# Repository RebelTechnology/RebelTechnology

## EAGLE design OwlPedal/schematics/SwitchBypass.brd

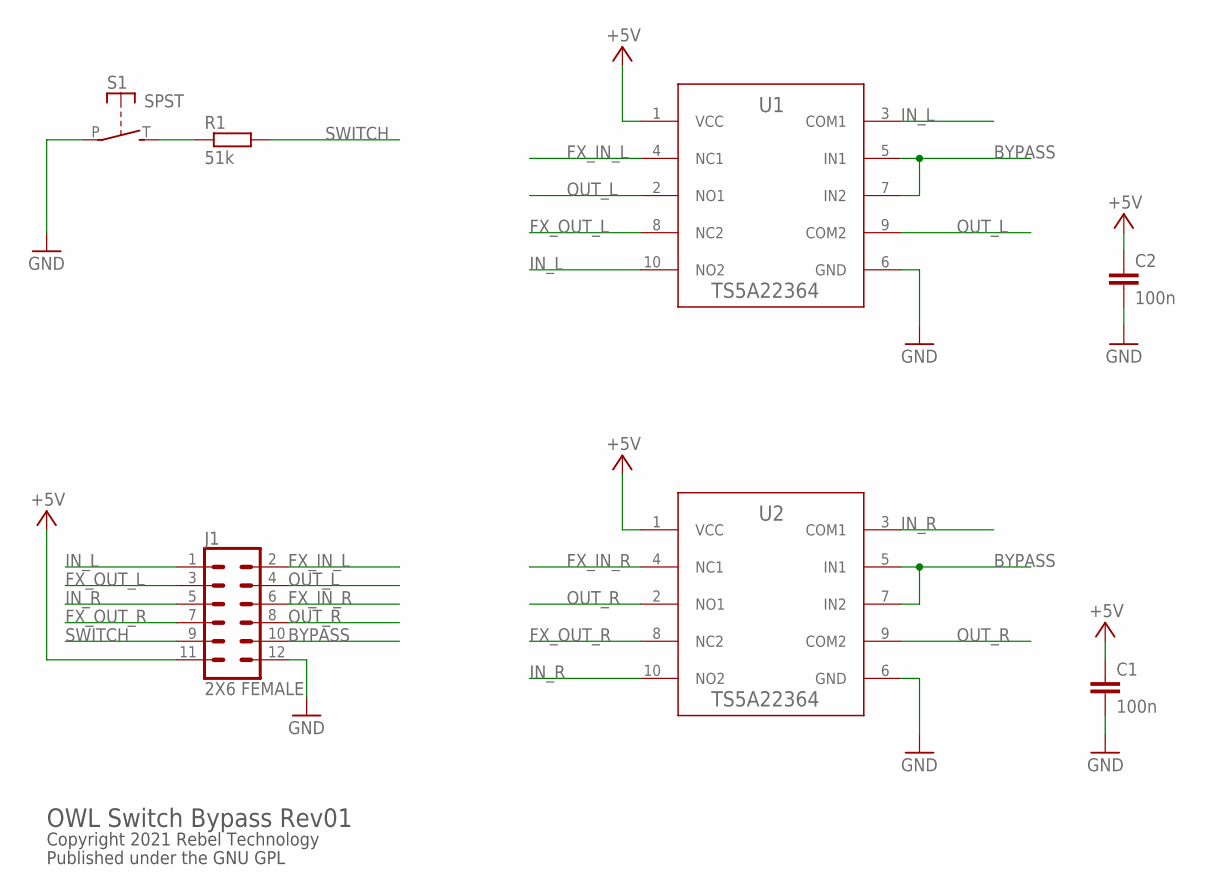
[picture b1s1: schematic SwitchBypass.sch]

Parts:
C1, C2: 100n; C0603
J1: 2X6 FEMALE; 2X6
R1: 51k; 0603
S1: SPST; JUDCOSPST
U1, U2: TS5A22364; DGS0010A_L

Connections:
+5V: C1.1, C2.1, J1.11, U1.1 (VCC), U2.1 (VCC)
BYPASS: J1.10, U1.5 (IN1), U1.7 (IN2), U2.5 (IN1), U2.7 (IN2)
FX_IN_L: J1.2, U1.4 (NC1)
FX_IN_R: J1.6, U2.4 (NC1)
FX_OUT_L: J1.3, U1.8 (NC2)
FX_OUT_R: J1.7, U2.8 (NC2)
GND: C1.2, C2.2, J1.12, S1.P, U1.6 (GND), U2.6 (GND)
IN_L: J1.1, U1.3 (COM1), U1.10 (NO2)
IN_R: J1.5, U2.3 (COM1), U2.10 (NO2)
unnamed: R1.1, S1.T (S)
OUT_L: J1.4, U1.2 (NO1), U1.9 (COM2)
OUT_R: J1.8, U2.2 (NO1), U2.9 (COM2)
SWITCH: J1.9, R1.2

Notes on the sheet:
Copyright 2021 Rebel Technology
Published under the GNU GPL
OWL Switch Bypass Rev01

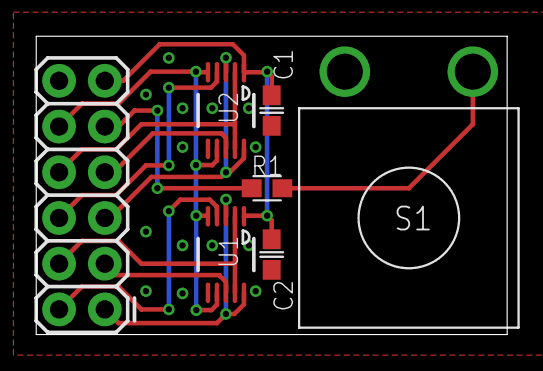
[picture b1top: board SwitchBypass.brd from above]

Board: 2 copper layers, 26.2 x 16.6 mm, 7 parts (0 on the bottom side), 13 nets.

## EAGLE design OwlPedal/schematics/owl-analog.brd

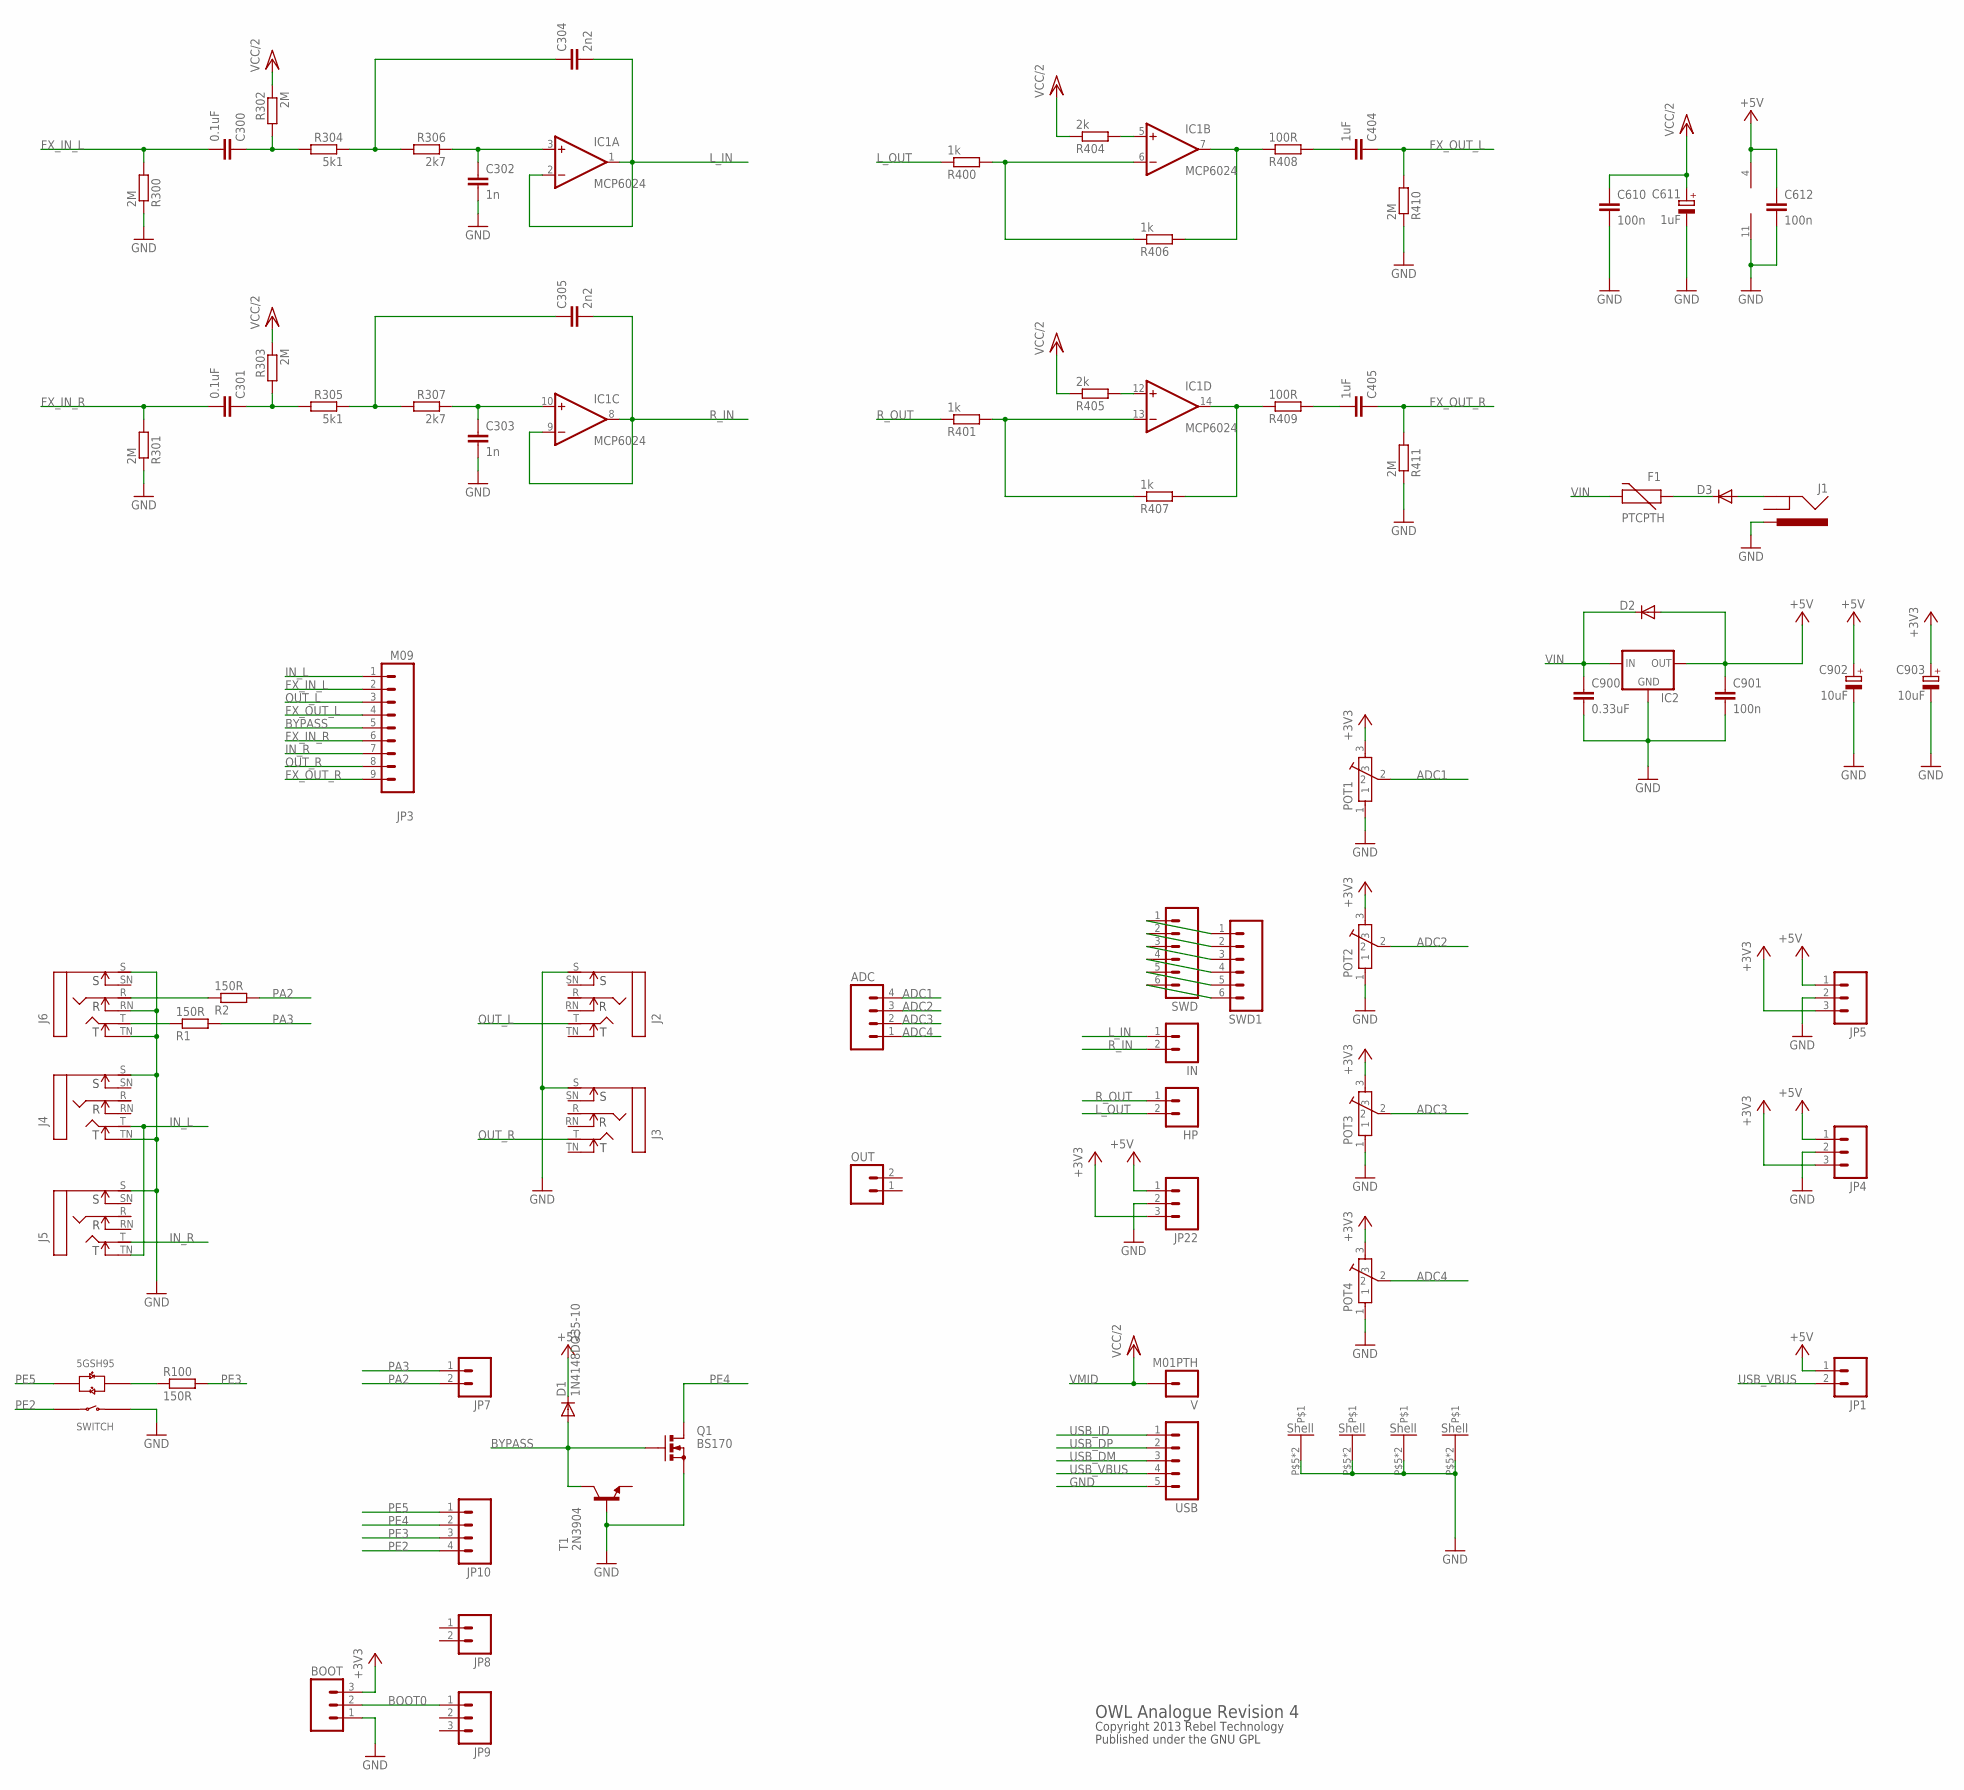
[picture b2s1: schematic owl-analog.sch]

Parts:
ADC: M04PTH; 1X04
BOOT: M03PTH; 1X03
C300, C301: 0.1uF; C5B3.5
C302, C303: 1n; C5B2.5
C304: 2n2; C5B2.5
C305: 2n2; C050-025X075
C404, C405: 1uF; C5B5
C610, C612, C901: 100n; C050-025X075
C611: 1uF; E2,5-7
C900: 0.33uF; C050-025X075
C902, C903: 10uF; E2,5-7
D1: 1N4148DO35-10; DO35-10
D2, D3: DIODE1N4001; DIODE-1N4001
F1: PTCPTH; PTC
HP: M02PTH; 1X02
IC1: MCP6024; DIL14
IC2: V_REG_78XX-TO-220; TO-220-ALT
IN: M02PTH; 1X02
J1: POWER_JACKPTH; POWER_JACK_PTH
J2, J3, J4, J5, J6: NEUTRIK_NMJ6HCD2; NMJ6HCD2
JP1, JP7, JP8: M02PTH; 1X02
JP3: M09; 1X09
JP4, JP5, JP9, JP22: M03PTH; 1X03
JP10: M04PTH; 1X04
OUT: M02PTH; 1X02
POT1, POT2, POT3, POT4: POT-ALPS-RK09L1140
Q1: BS170; SOT54E
R1, R2, R100: 150R; 0204/7
R300, R301, R302, R303, R410, R411: 2M; 0204/7
R304, R305: 5k1; 0204/7
R306, R307: 2k7; 0204/7
R400, R401, R406, R407: 1k; 0204/7
R404, R405: 2k; 0204/7
R408, R409: 100R; 0204/7
SWD, SWD1: M06SIP; 1X06
T1: 2N3904; TO92
U$1: 5GTH9
USB: M05PTH; 1X05
V: M01PTH; 1X01

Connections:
+3V3: BOOT.3, C903.+, JP4.3, JP5.3, JP22.3, POT1.3, POT2.3, POT3.3, POT4.3
+5V: C612.1, C901.1, C902.+, D1.C, D2.A, IC1.4 (V+), IC2.OUT, JP1.1, JP4.1, JP5.1, JP22.1
+5V/1: IC1.5 (+IN), R404.2
ADC1: ADC.4, POT1.2
ADC2: ADC.3, POT2.2
ADC3: ADC.2, POT3.2
ADC4: ADC.1, POT4.2
BOOT0: BOOT.2, JP9.1
BYPASS: D1.A, JP3.5, Q1.G, T1.1 (C)
FX_IN_L: C300.2, JP3.2, R300.2
FX_IN_R: C301.2, JP3.6, R301.2
FX_OUT_L: C404.1, JP3.4, R410.2
FX_OUT_R: C405.1, JP3.9, R411.2
GND: BOOT.1, C302.2, C303.2, C610.2, C611.-, C612.2, C900.2, C901.2, C902.-, C903.-, IC1.11 (V-), IC2.GND, J1.PWR, J2.S, J3.S, J4.S, J4.TN, J5.S, J6.RN, J6.S, J6.TN, JP4.2, JP5.2, JP22.2, POT1.1, POT1.P$5, POT1.P$6, POT2.1, POT2.P$5, POT2.P$6, POT3.1, POT3.P$5, POT3.P$6, POT4.1, POT4.P$5, POT4.P$6, Q1.S, R300.1, R301.1, R410.1, R411.1, T1.2 (B), U$1.1 (SWITCH_B), USB.5
IN_L: J4.T, J5.TN, JP3.1
IN_R: J5.T, JP3.7
L_IN: C304.2, IC1.1 (OUT), IC1.2 (-IN), IN.1
L_OUT: HP.2, R400.1
unnamed: D3.A, J1.GND
unnamed: IC1.12 (+IN), R405.2
unnamed: SWD.1, SWD1.1
unnamed: D3.C, F1.P$1 (1)
unnamed: SWD.2, SWD1.2
unnamed: SWD.3, SWD1.3
unnamed: SWD.4, SWD1.4
unnamed: SWD.5, SWD1.5
unnamed: SWD.6, SWD1.6
unnamed: R100.1, U$1.+3 (LED_R+)
unnamed: J6.R, R2.1
unnamed: J6.T, R1.1
unnamed: C300.1, R302.2, R304.2
unnamed: C405.2, R409.2
unnamed: C301.1, R303.2, R305.2
unnamed: C303.1, IC1.10 (+IN), R307.1
unnamed: C304.1, R304.1, R306.2
unnamed: C305.1, R305.1, R307.2
unnamed: C404.2, R408.2
unnamed: C302.1, IC1.3 (+IN), R306.1
unnamed: IC1.7 (OUT), R406.2, R408.1
unnamed: IC1.14 (OUT), R407.2, R409.1
unnamed: IC1.6 (-IN), R400.2, R406.1
unnamed: IC1.13 (-IN), R401.2, R407.1
OUT_L: J2.T, JP3.3
OUT_R: J3.T, JP3.8
PA2: JP7.2, R2.2
PA3: JP7.1, R1.2
PE2: JP10.4, U$1.4 (SWITCH_A)
PE3: JP10.3, R100.2
PE4: JP10.2, Q1.D
PE5: JP10.1, U$1.-2 (LED_G+)
R_IN: C305.2, IC1.8 (OUT), IC1.9 (-IN), IN.2
R_OUT: HP.1, R401.1
USB_DM: USB.3
USB_DP: USB.2
USB_ID: USB.1
USB_VBUS: JP1.2, USB.4
VIN: C900.1, D2.C, F1.P$2 (2), IC2.IN
VMID: C610.1, C611.+, R302.1, R303.1, R404.1, R405.1, V.1

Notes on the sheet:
Copyright 2013 Rebel Technology
Published under the GNU GPL
OWL Analogue Revision 4

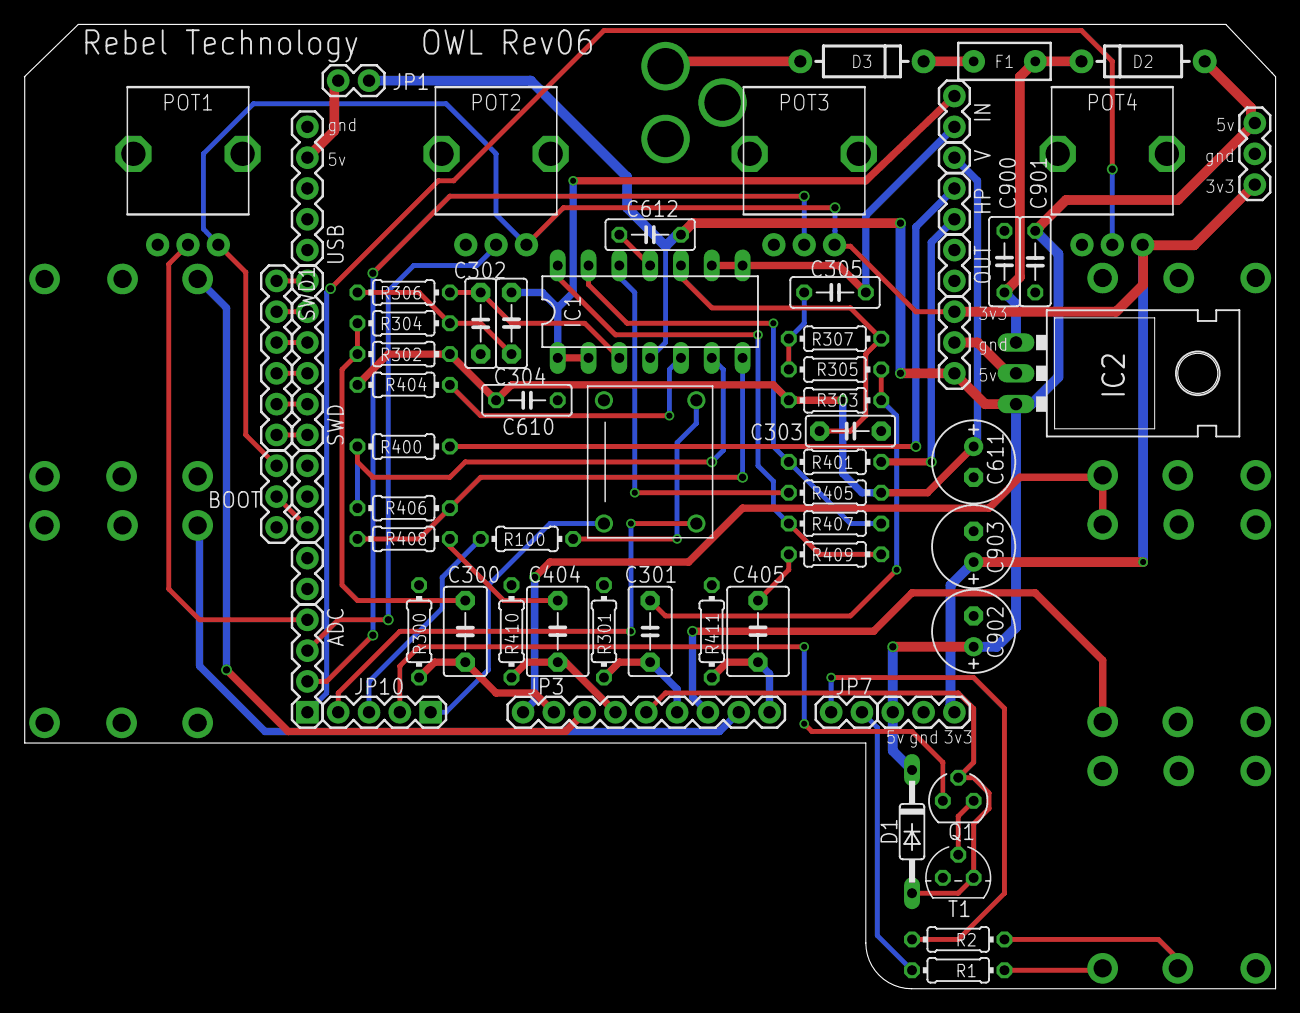
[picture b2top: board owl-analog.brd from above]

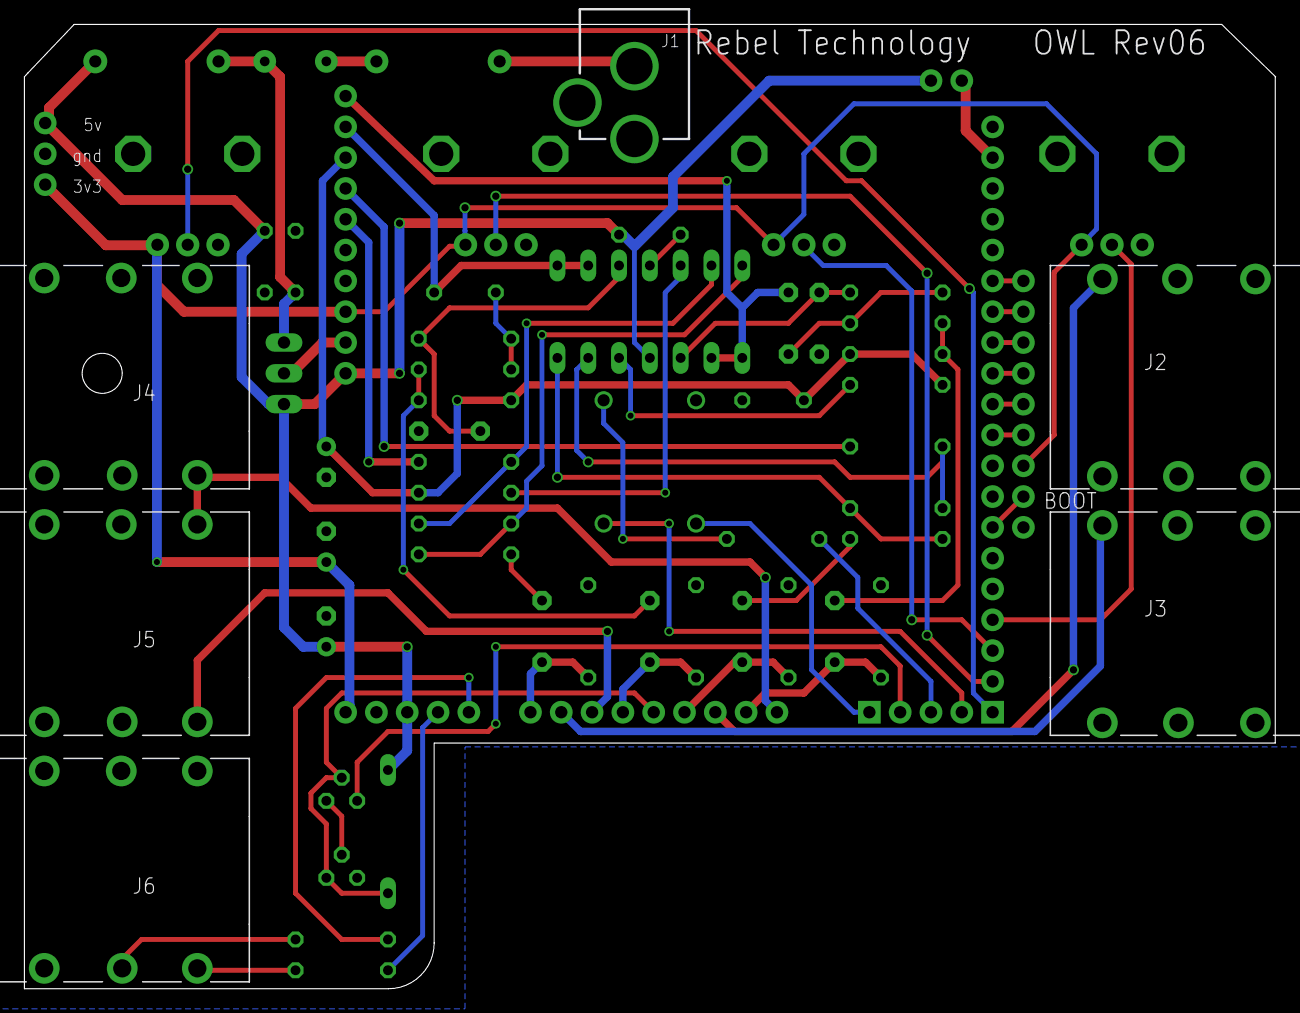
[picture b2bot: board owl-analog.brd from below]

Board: 2 copper layers, 103.1 x 79.5 mm, 73 parts (6 on the bottom side), 55 nets.

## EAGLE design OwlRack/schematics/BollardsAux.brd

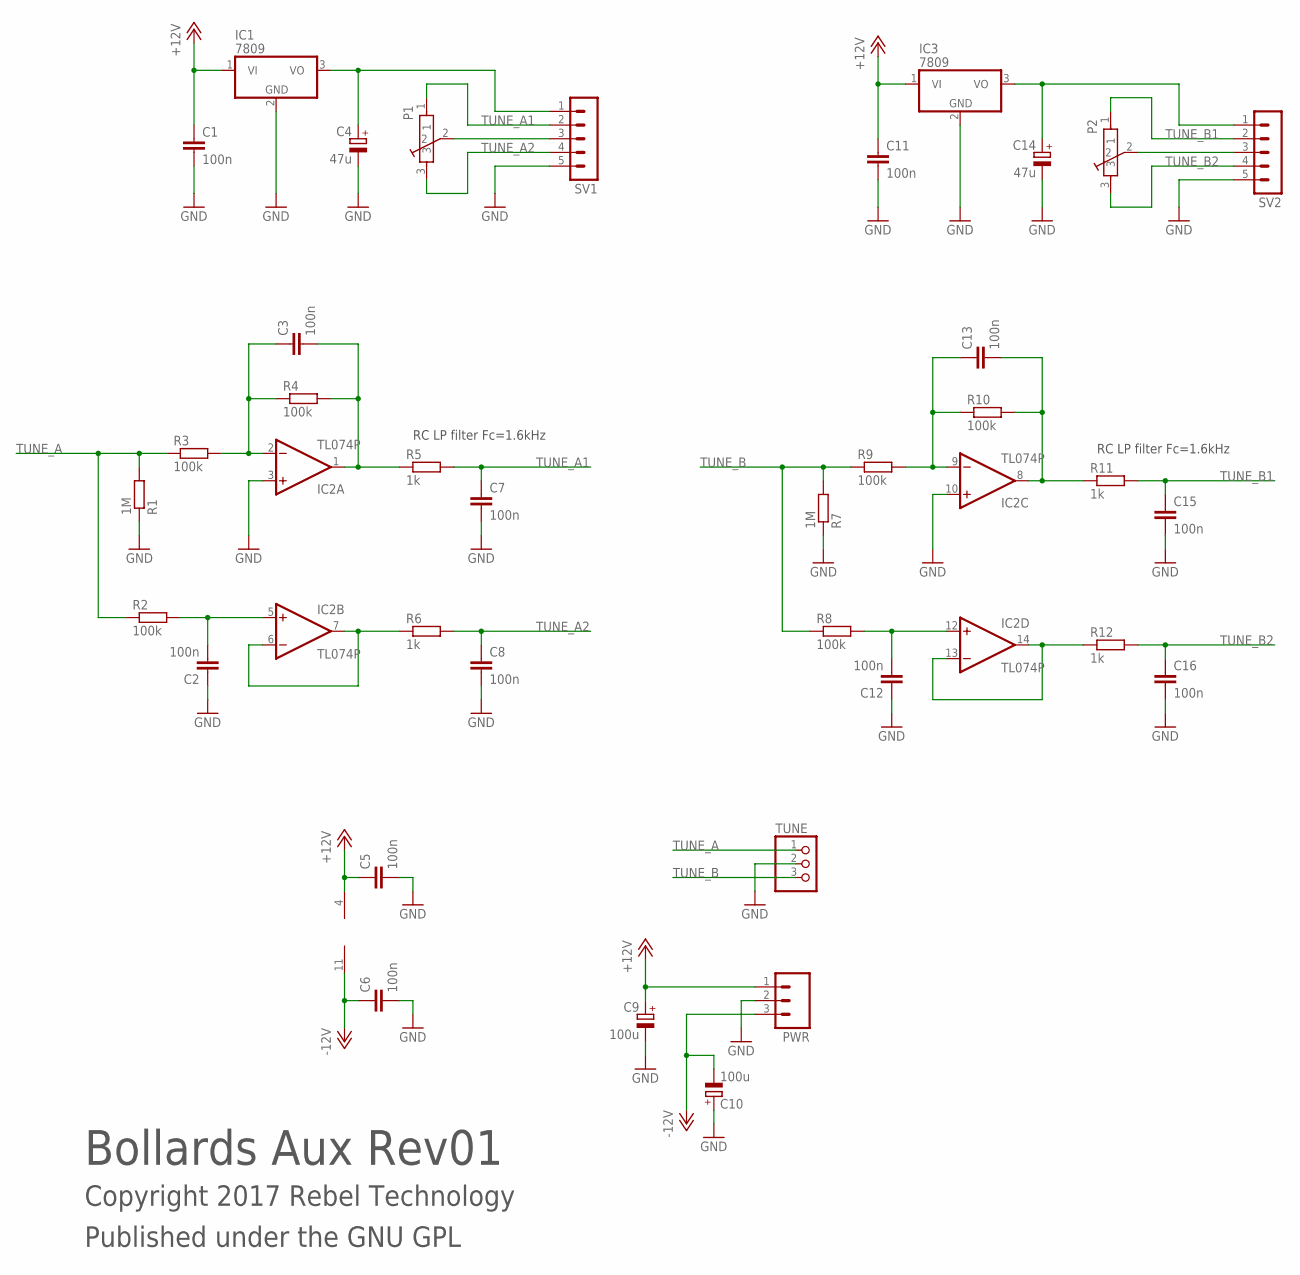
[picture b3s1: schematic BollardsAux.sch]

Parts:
C1, C2, C3, C5, C6, C7, C8, C11, C12, C13, C15, C16: 100n; C050-025X075
C4, C14: 47u; E2,5-7
C9, C10: 100u; E2,5-7
IC1, IC3: 7809; TO220H
IC2: TL074P; DIL14
P1, P2: 100k; POT-BOURNS-PTD901
PWR: M03PTH; 1X03
R1, R7: 1M; 0204/7
R2, R3, R4, R8, R9, R10: 100k; 0204/7
R5, R6, R11, R12: 1k; 0204/7
SV1, SV2: MA05-1
TUNE: CON-JST-1X03PH-TH; JST-B3B-PH-KL

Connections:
+12V: C1.1, C5.1, C9.+, C11.1, IC1.1 (VI), IC2.4 (V+), IC3.1 (VI), PWR.1
-12V: C6.1, C10.-, IC2.11 (V-), PWR.3
GND: C1.2, C2.1, C4.-, C5.2, C6.2, C7.2, C8.2, C9.-, C10.+, C11.2, C12.1, C14.-, C15.2, C16.2, IC1.2 (GND), IC2.3 (+IN), IC2.10 (+IN), IC3.2 (GND), PWR.2, R1.1, R7.1, SV1.5, SV2.5, TUNE.2
unnamed: C2.2, IC2.5 (+IN), R2.2
unnamed: C4.+, IC1.3 (VO), SV1.1
unnamed: P1.2, SV1.3
unnamed: C13.1, IC2.9 (-IN), R9.2, R10.1
unnamed: C13.2, IC2.8 (OUT), R10.2, R11.1
unnamed: IC2.6 (-IN), IC2.7 (OUT), R6.1
unnamed: C14.+, IC3.3 (VO), SV2.1
unnamed: P2.2, SV2.3
unnamed: C12.2, IC2.12 (+IN), R8.2
unnamed: IC2.13 (-IN), IC2.14 (OUT), R12.1
unnamed: C3.1, IC2.2 (-IN), R3.2, R4.1
unnamed: C3.2, IC2.1 (OUT), R4.2, R5.1
TUNE_A: R1.2, R2.1, R3.1, TUNE.1
TUNE_A1: C7.1, P1.1, R5.2, SV1.2
TUNE_A2: C8.1, P1.3, R6.2, SV1.4
TUNE_B: R7.2, R8.1, R9.1, TUNE.3
TUNE_B1: C15.1, P2.1, R11.2, SV2.2
TUNE_B2: C16.1, P2.3, R12.2, SV2.4

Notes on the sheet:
Bollards Aux Rev01
Copyright 2017 Rebel Technology
Published under the GNU GPL
RC LP filter Fc=1.6kHz

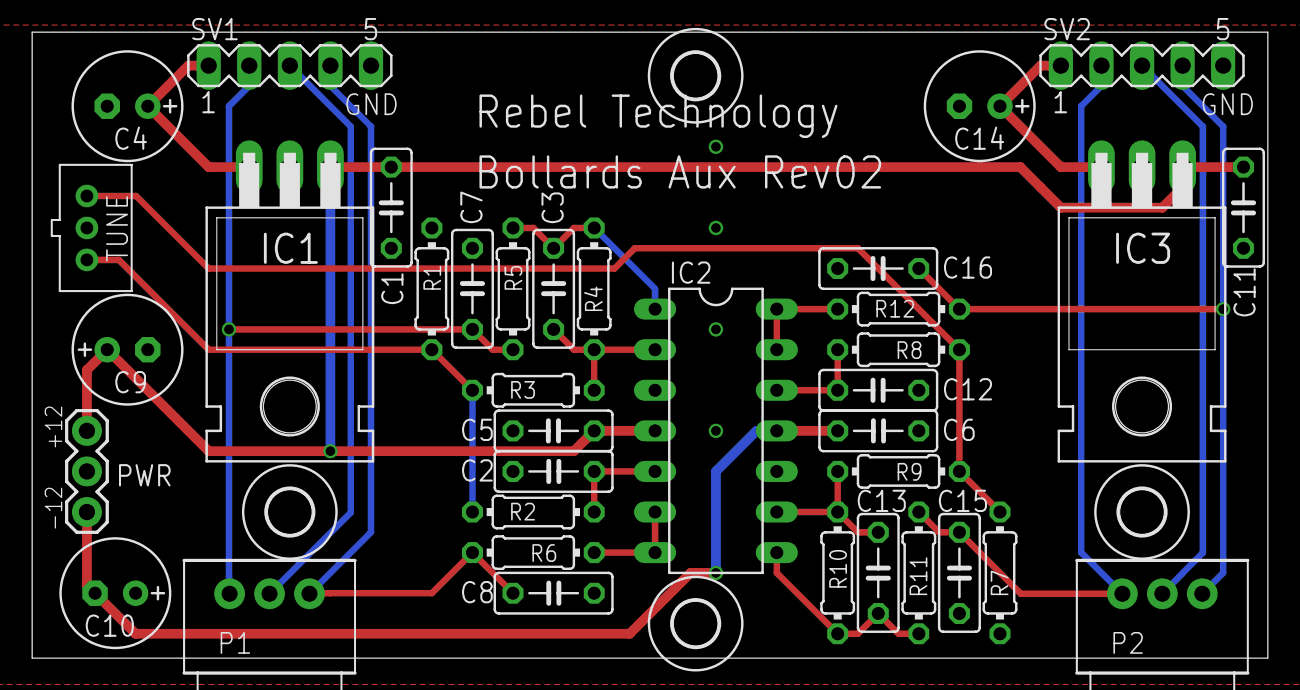
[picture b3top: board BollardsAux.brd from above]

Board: 2 copper layers, 77.3 x 39.2 mm, 41 parts (0 on the bottom side), 21 nets.

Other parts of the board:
U$1, U$3, U$4, U$6: 2,8

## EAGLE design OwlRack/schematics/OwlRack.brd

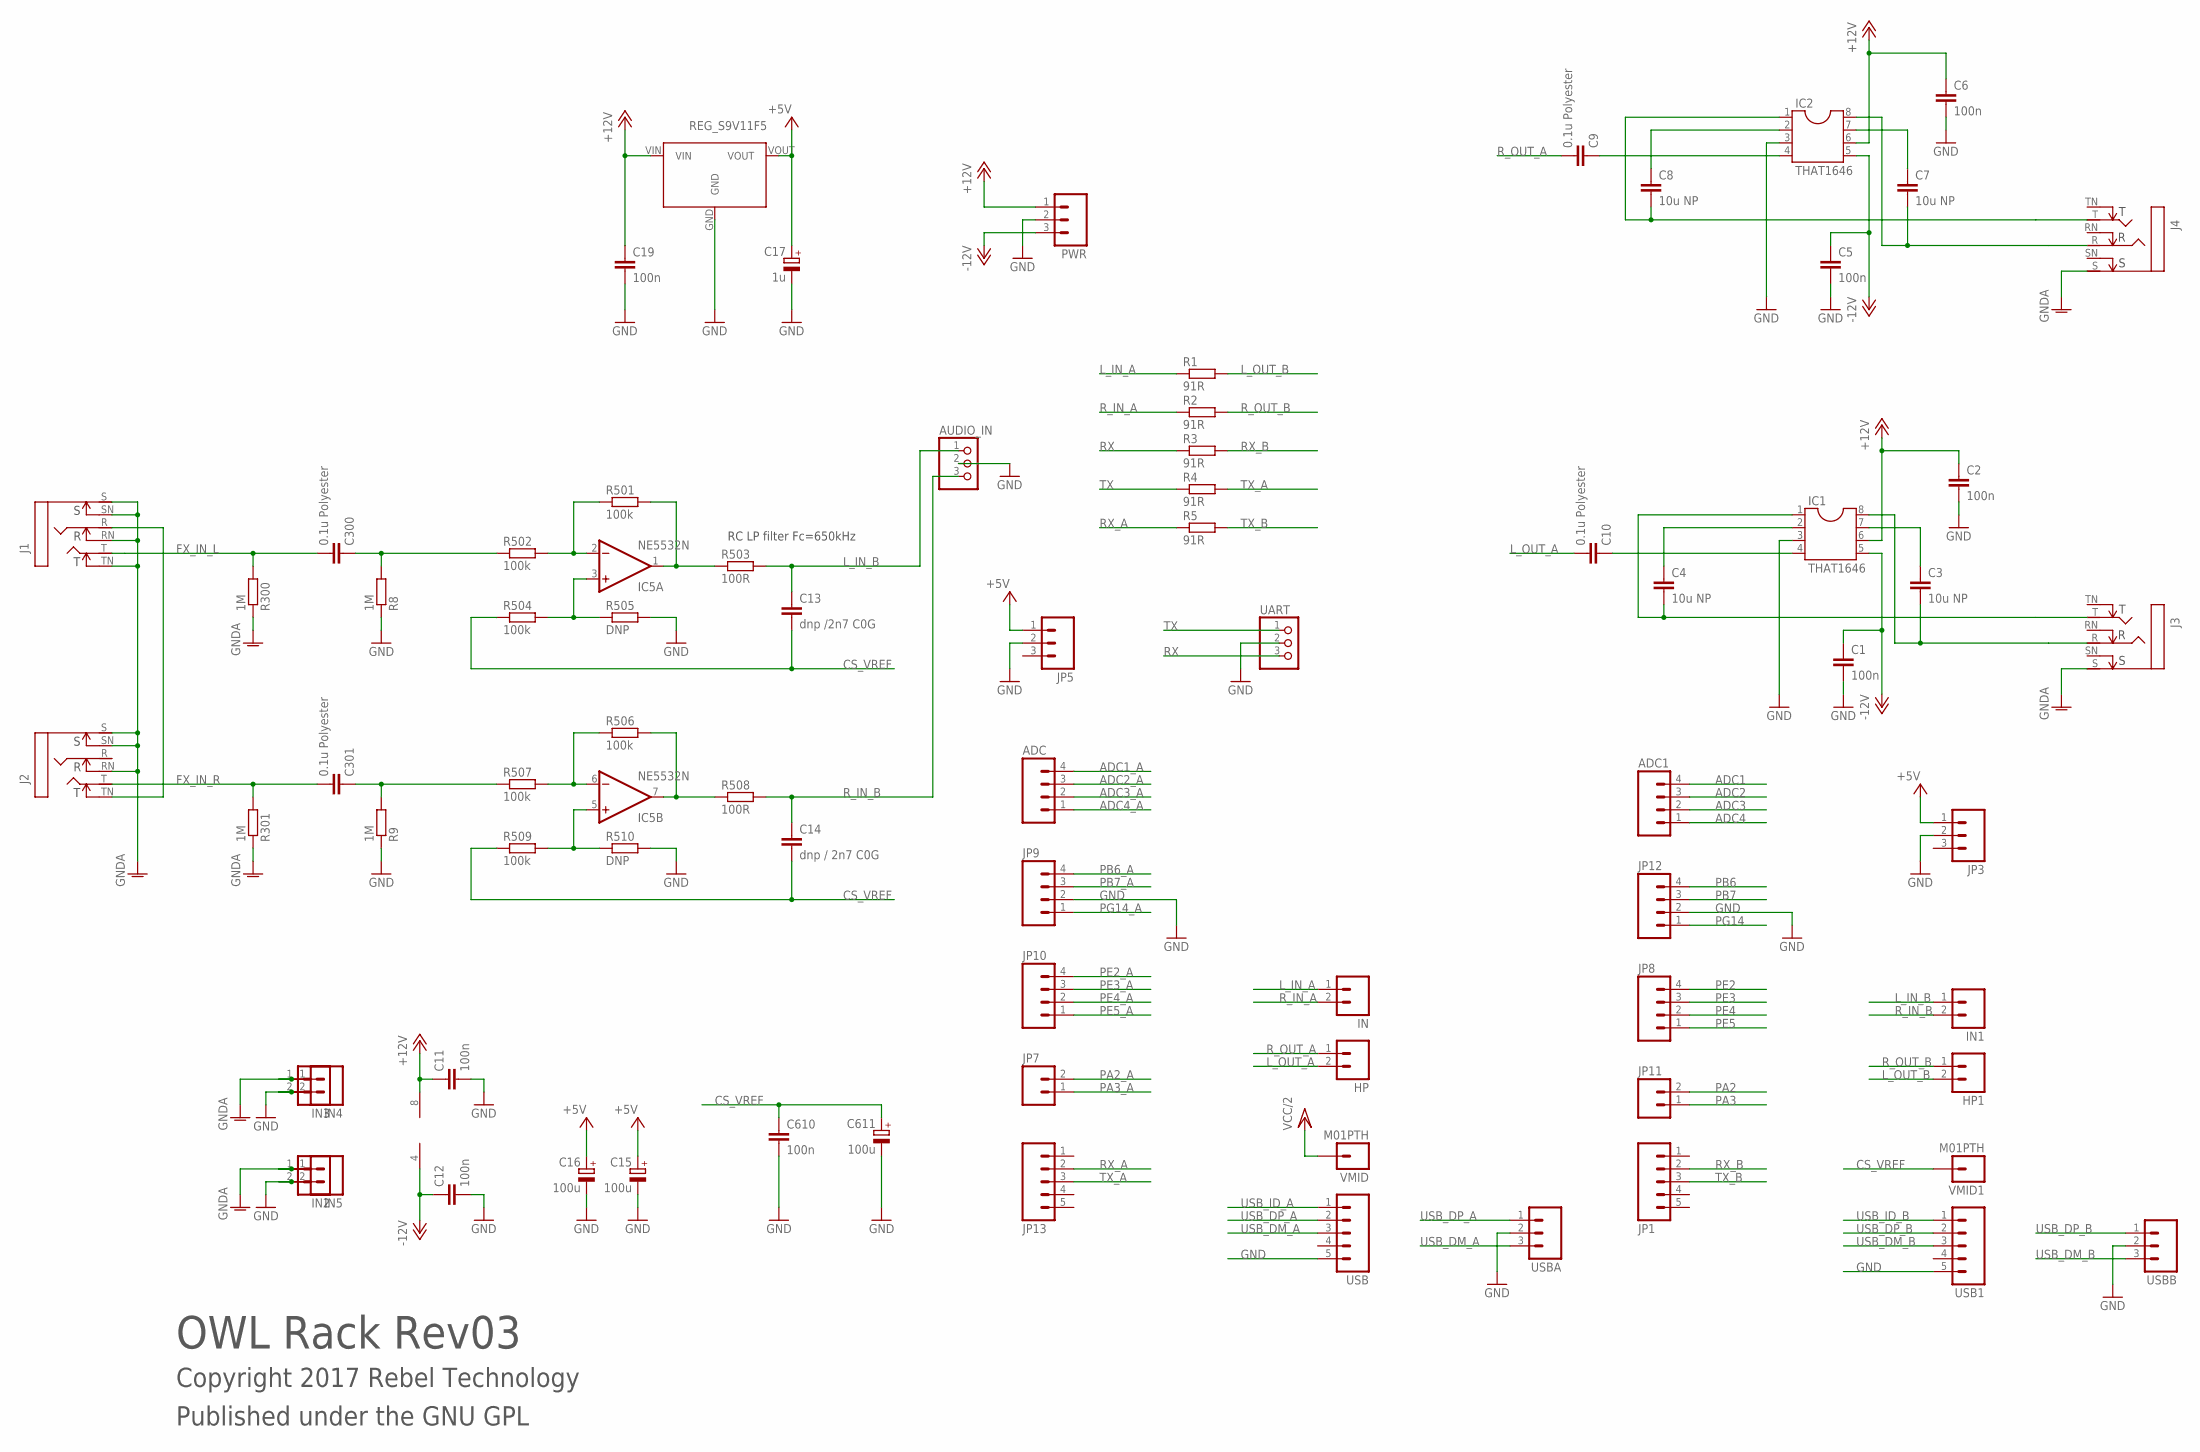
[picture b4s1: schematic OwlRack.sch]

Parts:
ADC, ADC1: M04PTH; 1X04
AUDIO_IN: CON-JST-1X03PH-TH; JST-B3B-PH-KL
C1, C2, C5, C6, C11, C12, C19, C610: 100n; C050-025X075
C3, C4, C7, C8: 10u NP; C050-025X075
C9, C10, C300, C301: 0.1u Polyester; C5B3.5
C13: dnp /2n7 C0G; C050-025X075
C14: dnp / 2n7 C0G; C050-025X075
C15, C16, C611: 100u; E2,5-7
C17: 1u; E2,5-7
HP, HP1: M02PTH; 1X02
IC1, IC2: THAT1646; DIL08
IC3: REG_S9V11F5
IC5: NE5532N; DIL08
IN, IN1, IN2, IN3, IN4, IN5: M02PTH; 1X02
J1, J2, J3, J4: NEUTRIK_NRJ6HFSTD; NRJ6HF
JP1, JP13: M05PTH; 1X05
JP3, JP5: M03PTH; 1X03
JP7, JP11: M02PTH; 1X02
JP8, JP9, JP10, JP12: M04PTH; 1X04
PWR: M03PTH; 1X03
R1, R2, R3, R4, R5: 91R; 0204/7
R8, R9, R300, R301: 1M; 0204/7
R501, R502, R504, R506, R507, R509: 100k; 0204/7
R503, R508: 100R; 0204/7
R505, R510: DNP; 0204/7
UART: CON-JST-1X03PH-TH; JST-B3B-PH-KL
USB, USB1: M05PTH; 1X05
USBA: M03PTH; 1X03
USBB: M03PTH; 1X03
VMID, VMID1: M01PTH; 1X01

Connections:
+5V: C15.+, C16.+, C17.+, IC3.VOUT, JP3.1, JP5.1
+12V: C2.1, C6.1, C11.1, C19.1, IC1.6, IC2.6, IC3.VIN, IC5.8 (V+), PWR.1
-12V: C1.1, C5.1, C12.1, IC1.5, IC2.5, IC5.4 (V-), PWR.3
ADC1: ADC1.4
ADC1_A: ADC.4
ADC2: ADC1.3
ADC2_A: ADC.3
ADC3: ADC1.2
ADC3_A: ADC.2
ADC4: ADC1.1
ADC4_A: ADC.1
CS_VREF: C13.2, C14.2, C610.1, C611.+, R504.1, R509.1, VMID1.1
FX_IN_L: C300.2, J1.T, R300.2
FX_IN_R: C301.2, J2.T, R301.2
GND: AUDIO_IN.2, C1.2, C2.2, C5.2, C6.2, C11.2, C12.2, C15.-, C16.-, C17.-, C19.2, C610.2, C611.-, IC1.3, IC2.3, IC3.GND, IN2.2, IN3.2, IN4.2, IN5.2, JP3.2, JP5.2, JP9.2, JP12.2, PWR.2, R8.1, R9.1, R505.2, R510.2, UART.2, USB.5, USB1.5, USBA.2, USBB.2
GNDA: IN2.1, IN3.1, IN4.1, IN5.1, J1.RN, J1.S, J1.SN, J1.TN, J2.RN, J2.S, J2.SN, J3.S, J4.S, R300.1, R301.1
L_IN_A: IN.1, R1.1
L_IN_B: AUDIO_IN.1, C13.1, IN1.1, R503.2
L_OUT_A: C10.2, HP.2
L_OUT_B: HP1.2, R1.2
unnamed: IC5.7 (OUT), R506.2, R508.1
unnamed: C3.2, IC1.8, J3.R
unnamed: C4.2, IC1.1, J3.T
unnamed: C3.1, IC1.7
unnamed: C4.1, IC1.2
unnamed: J1.R, J2.TN
unnamed: C9.1, IC2.4
unnamed: C7.1, IC2.7
unnamed: C10.1, IC1.4
unnamed: C8.1, IC2.2
unnamed: C7.2, IC2.8, J4.R
unnamed: C8.2, IC2.1, J4.T
unnamed: C300.1, R8.2, R502.1
unnamed: C301.1, R9.2, R507.1
unnamed: IC5.3 (+IN), R504.2, R505.1
unnamed: IC5.2 (-IN), R501.1, R502.2
unnamed: IC5.1 (OUT), R501.2, R503.1
unnamed: IC5.5 (+IN), R509.2, R510.1
unnamed: IC5.6 (-IN), R506.1, R507.2
PA2: JP11.2
PA2_A: JP7.2
PA3: JP11.1
PA3_A: JP7.1
PB6: JP12.4
PB6_A: JP9.4
PB7: JP12.3
PB7_A: JP9.3
PE2: JP8.4
PE2_A: JP10.4
PE3: JP8.3
PE3_A: JP10.3
PE4: JP8.2
PE4_A: JP10.2
PE5: JP8.1
PE5_A: JP10.1
PG14: JP12.1
PG14_A: JP9.1
RX: R3.1, UART.3
RX_A: JP13.2, R5.1
RX_B: JP1.2, R3.2
R_IN_A: IN.2, R2.1
R_IN_B: AUDIO_IN.3, C14.1, IN1.2, R508.2
R_OUT_A: C9.2, HP.1
R_OUT_B: HP1.1, R2.2
TX: R4.1, UART.1
TX_A: JP13.3, R4.2
TX_B: JP1.3, R5.2
USB_DM_A: USB.3, USBA.3
USB_DM_B: USB1.3, USBB.3
USB_DP_A: USB.2, USBA.1
USB_DP_B: USB1.2, USBB.1
USB_ID_A: USB.1
USB_ID_B: USB1.1
VCC/2: VMID.1

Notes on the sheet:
OWL Rack Rev03
Copyright 2017 Rebel Technology
Published under the GNU GPL
RC LP filter Fc=650kHz

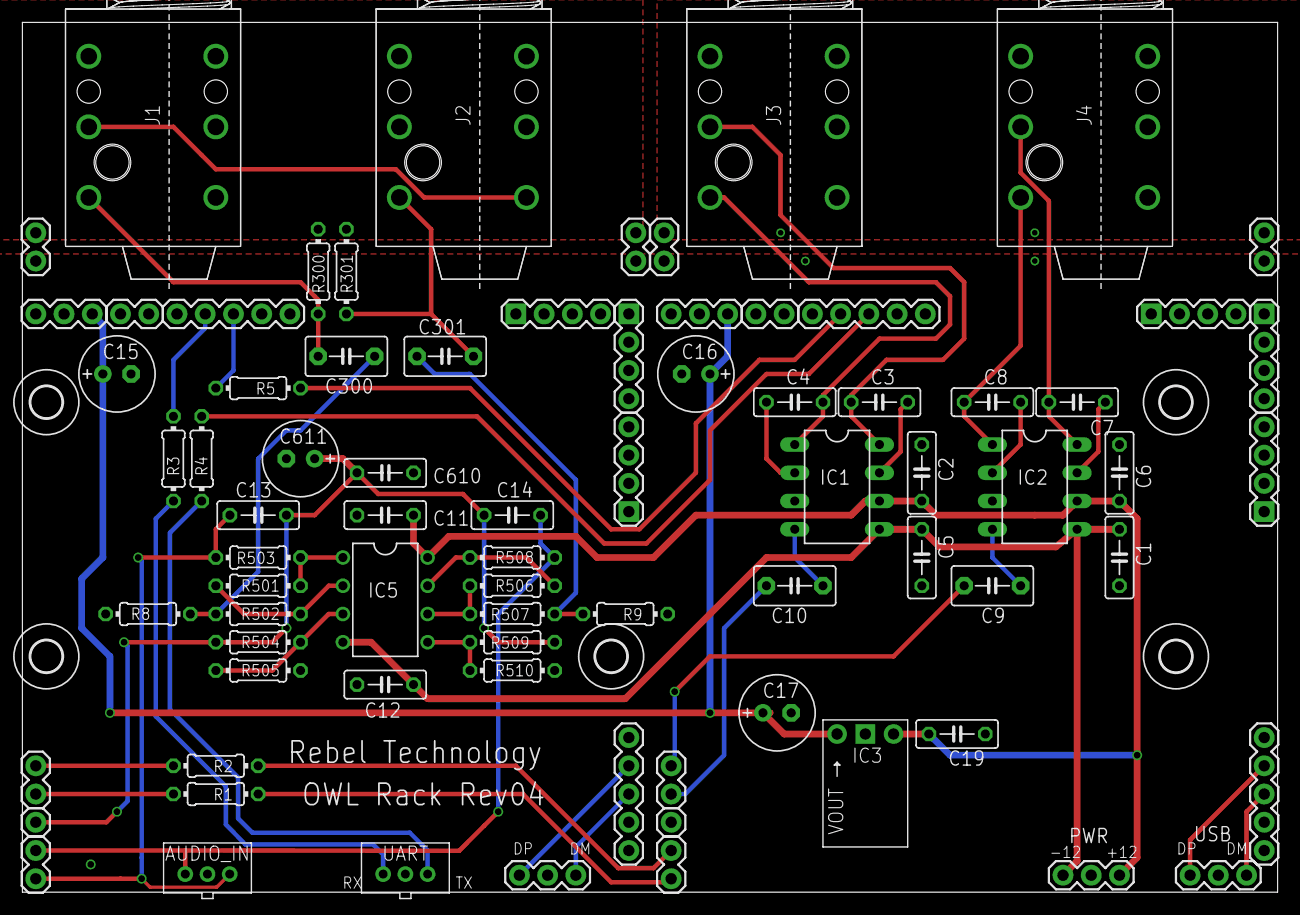
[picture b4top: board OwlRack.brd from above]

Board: 2 copper layers, 112.9 x 78.2 mm, 83 parts (0 on the bottom side), 45 nets.

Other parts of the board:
U$1, U$3, U$4, U$5, U$6: 2,8

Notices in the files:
parts and their libraries:
SparkFun-Connectors: Licensing: Creative Commons ShareAlike 4.0 International - https://creativecommons.org/licenses/by-sa/4.0
SparkFun: Licensing: CC v3.0 Share-Alike You are welcome to use this library for commercial purposes.
